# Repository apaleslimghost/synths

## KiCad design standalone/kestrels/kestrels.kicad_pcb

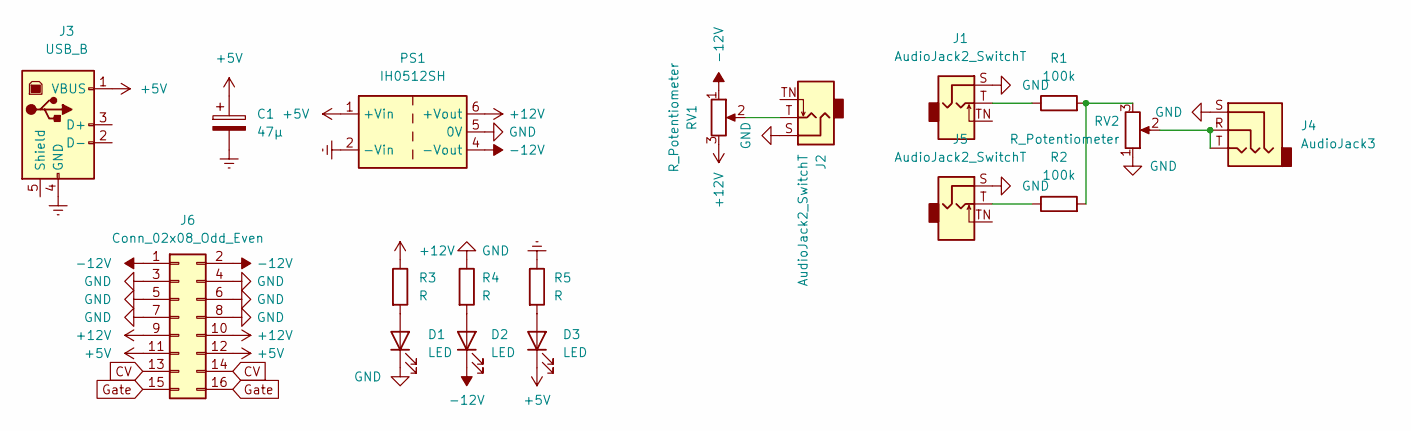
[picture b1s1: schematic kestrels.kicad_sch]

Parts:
C1: 47μ; CP_Radial_D5.0mm_P2.50mm
D1, D2, D3: LED; LED_D3.0mm
J1, J2, J5: AudioJack2_SwitchT; Jack_3.5mm_QingPu_WQP-PJ398SM_Vertical
J3: USB_B; USB_B_Lumberg_2411_02_Horizontal
J4: AudioJack3; Jack_3.5mm_QingPu_WQP-PJ366ST_Vertical
J6: Conn_02x08_Odd_Even; PinHeader_2x08_P2.54mm_Vertical
PS1: IH0512SH; Converter_DCDC_XP_POWER-IHxxxxSH_THT
R1, R2: 100k; R_Axial_DIN0207_L6.3mm_D2.5mm_P7.62mm_Horizontal
R3, R4, R5: R; R_Axial_DIN0207_L6.3mm_D2.5mm_P7.62mm_Horizontal
RV1, RV2: R_Potentiometer; Potentiometer_Alpha_RD901F-40-00D_Single_Vertical

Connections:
+5V: C1.1, D3.1 (K), J3.1 (VBUS), J6.11, J6.12, PS1.1 (+Vin)
+12V: J6.9, J6.10, PS1.6 (+Vout), R3.1, RV1.3
-12V: D2.1 (K), J6.1, J6.2, PS1.4 (-Vout), RV1.1
CV: J6.13, J6.14
Earth: C1.2, J3.4 (GND), PS1.2 (-Vin), R5.1
GND: D1.1 (K), J1.S, J2.S, J4.S, J5.S, J6.3, J6.4, J6.5, J6.6, J6.7, J6.8, PS1.5 (0V), R4.1, RV2.1
Gate: J6.15, J6.16
unnamed: D1.2 (A), R3.2
unnamed: D2.2 (A), R4.2
unnamed: D3.2 (A), R5.2
unnamed: J1.T, R1.1
unnamed: J2.T, RV1.2
unnamed: J4.R, J4.T, RV2.2
unnamed: J5.T, R2.1
unnamed: R1.2, R2.2, RV2.3

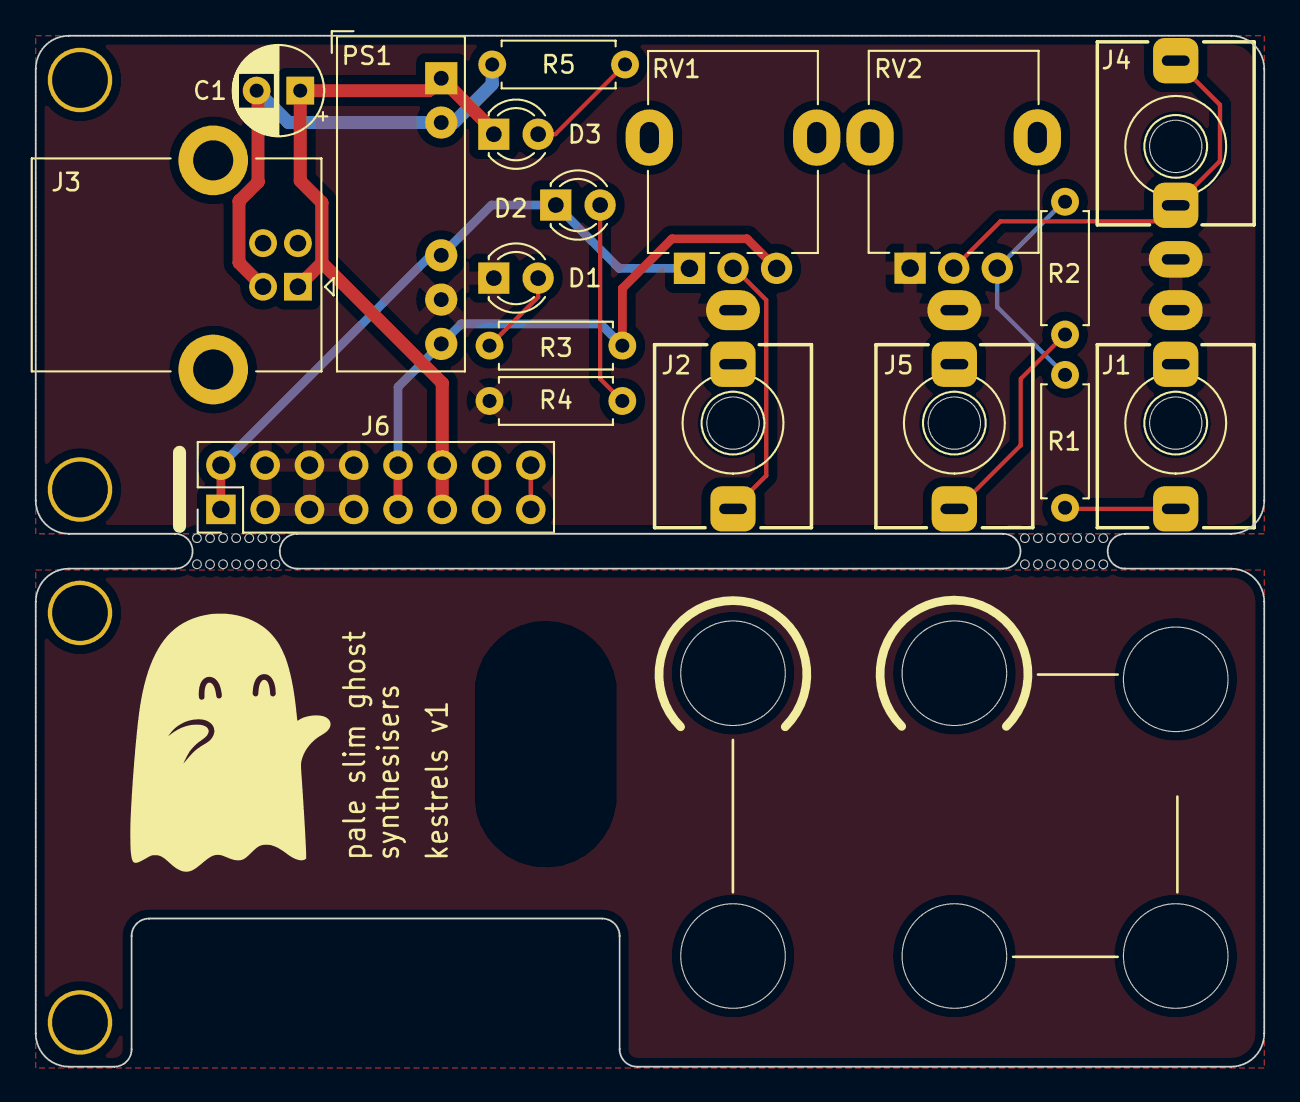
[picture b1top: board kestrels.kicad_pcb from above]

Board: 2 copper layers, 70.5 x 59.2 mm, 20 parts (0 on the bottom side), 15 nets.

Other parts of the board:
mouse-bite-2mm-slot, mouse-bite-2mm-slot#2: VAL**; mousebite-2x5mm

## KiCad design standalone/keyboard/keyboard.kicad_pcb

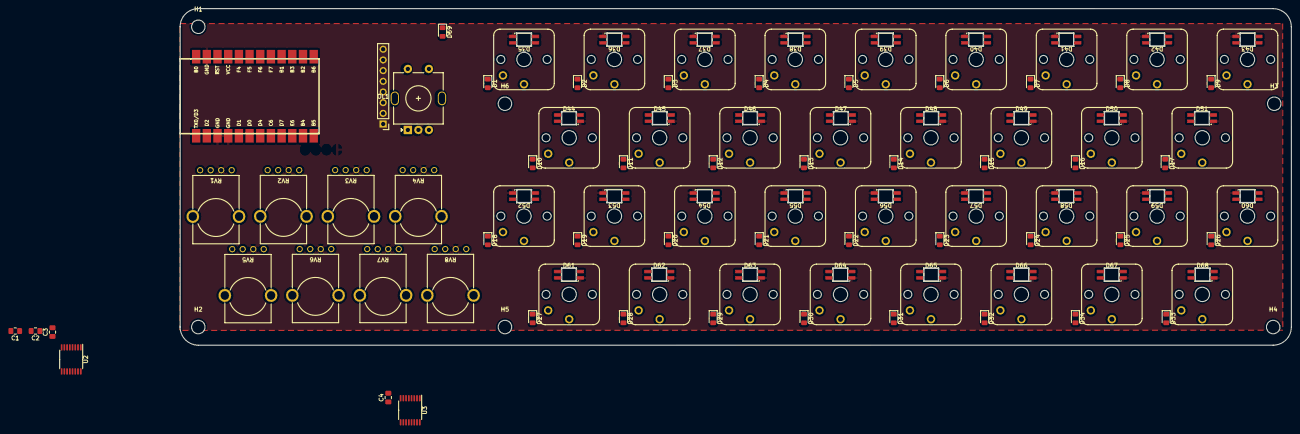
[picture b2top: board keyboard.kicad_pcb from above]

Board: 2 copper layers, 264.2 x 80.0 mm, 126 parts (0 on the bottom side), 104 nets, no tracks yet.

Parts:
C1, C2, C3, C4: C; C_0805_2012Metric_Pad1.18x1.45mm_HandSolder
D1, D2, D3, D4, D5, D6, D7, D8, D9, D10, D11, D12, D13, D14, D15, D16, D17, D18, D19, D20, D21, D22, D23, D24, D25, D26, D27, D28, D29, D30, D31, D32, D33, D34, D69: D; D_0805_2012Metric_Pad1.15x1.40mm_HandSolder
D35, D36, D37, D38, D39, D40, D41, D42, D43, D44, D45, D46, D47, D48, D49, D50, D51, D52, D53, D54, D55, D56, D57, D58, D59, D60, D61, D62, D63, D64, D65, D66, D67, D68: SK6812MINI; SK6812MINI-E
H1, H2, H3, H4, H5, H6: MountingHole; MountingHole_3.2mm_M3
OL1: WaveShare_OLED; WaveShare OLED 1.5 inch
RV1, RV2, RV3, RV4, RV5, RV6, RV7, RV8: R_Potentiometer_Endless; Alpha RV112FF
SW1, SW2, SW3, SW4, SW5, SW6, SW7, SW8, SW9, SW10, SW11, SW12, SW13, SW14, SW15, SW16, SW17, SW18, SW19, SW20, SW21, SW22, SW23, SW24, SW25, SW26, SW27, SW28, SW29, SW30, SW31, SW32, SW33, SW34: SW_Push; Kailh Choc V1
SW35: RotaryEncoder_Switch; RotaryEncoder_EC11
U1: ProMicro; Elite-C-castellated-24pin
U2, U3: ADS7828; TSSOP-16_4.4x5mm_P0.65mm

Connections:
+5V: C3.1, C4.1, D35.1 (VDD), D36.1 (VDD), D37.1 (VDD), D38.1 (VDD), D39.1 (VDD), D40.1 (VDD), D41.1 (VDD), D42.1 (VDD), D43.1 (VDD), D44.1 (VDD), D45.1 (VDD), D46.1 (VDD), D47.1 (VDD), D48.1 (VDD), D49.1 (VDD), D50.1 (VDD), D51.1 (VDD), D52.1 (VDD), D53.1 (VDD), D54.1 (VDD), D55.1 (VDD), D56.1 (VDD), D57.1 (VDD), D58.1 (VDD), D59.1 (VDD), D60.1 (VDD), D61.1 (VDD), D62.1 (VDD), D63.1 (VDD), D64.1 (VDD), D65.1 (VDD), D66.1 (VDD), D67.1 (VDD), D68.1 (VDD), RV1.3, RV2.3, RV3.3, RV4.3, RV5.3, RV6.3, RV7.3, RV8.3, U1.21 (VCC), U2.10 (REF), U2.16 (VDD), U3.10 (REF), U3.16 (VDD)
Col 1: SW1.1, SW10.1, SW18.1, SW27.1, U1.20 (F4)
Col 2: SW2.1, SW11.1, SW19.1, SW28.1, U1.19 (F5)
Col 3: SW3.1, SW12.1, SW20.1, SW29.1, U1.18 (F6)
Col 4: SW4.1, SW13.1, SW21.1, SW30.1, U1.17 (F7)
Col 5: SW5.1, SW14.1, SW22.1, SW31.1, U1.16 (B1)
Col 6: SW6.1, SW15.1, SW23.1, SW32.1, U1.15 (B3)
Col 7: SW7.1, SW16.1, SW24.1, SW33.1, U1.14 (B2)
Col 8: SW8.1, SW17.1, SW25.1, SW34.1, U1.13 (B6)
Col 9: SW9.1, SW26.1, SW35.S2, U1.12 (B5)
Enc A: C1.2, SW35.A, U1.1 (TX)
Enc B: C2.1, SW35.B, U1.2 (RX)
GND: C1.1, C2.2, C3.2, C4.2, D35.3 (VSS), D36.3 (VSS), D37.3 (VSS), D38.3 (VSS), D39.3 (VSS), D40.3 (VSS), D41.3 (VSS), D42.3 (VSS), D43.3 (VSS), D44.3 (VSS), D45.3 (VSS), D46.3 (VSS), D47.3 (VSS), D48.3 (VSS), D49.3 (VSS), D50.3 (VSS), D51.3 (VSS), D52.3 (VSS), D53.3 (VSS), D54.3 (VSS), D55.3 (VSS), D56.3 (VSS), D57.3 (VSS), D58.3 (VSS), D59.3 (VSS), D60.3 (VSS), D61.3 (VSS), D62.3 (VSS), D63.3 (VSS), D64.3 (VSS), D65.3 (VSS), D66.3 (VSS), D67.3 (VSS), D68.3 (VSS), RV1.1, RV2.1, RV3.1, RV4.1, RV5.1, RV6.1, RV7.1, RV8.1, SW35.C, U1.3 (GND), U1.4 (GND), U1.23 (GND), U2.9 (GND), U2.11 (COM), U2.12 (A0), U2.13 (A1), U3.9 (GND), U3.11 (COM), U3.12 (A0), U3.13 (A1)
LED: D35.4 (DIN), U1.11 (B4)
unnamed: D1.1 (K), SW1.2
unnamed: D2.1 (K), SW2.2
unnamed: D3.1 (K), SW3.2
unnamed: D4.1 (K), SW4.2
unnamed: D5.1 (K), SW5.2
unnamed: D6.1 (K), SW6.2
unnamed: D7.1 (K), SW7.2
unnamed: D8.1 (K), SW8.2
unnamed: D9.1 (K), SW9.2
unnamed: D10.1 (K), SW10.2
unnamed: D11.1 (K), SW11.2
unnamed: D12.1 (K), SW12.2
unnamed: D13.1 (K), SW13.2
unnamed: D14.1 (K), SW14.2
unnamed: D15.1 (K), SW15.2
unnamed: D16.1 (K), SW16.2
unnamed: D17.1 (K), SW17.2
unnamed: D18.1 (K), SW18.2
unnamed: D19.1 (K), SW19.2
unnamed: D20.1 (K), SW20.2
unnamed: D21.1 (K), SW21.2
unnamed: D22.1 (K), SW22.2
unnamed: D23.1 (K), SW23.2
unnamed: D24.1 (K), SW24.2
unnamed: D25.1 (K), SW25.2
unnamed: D26.1 (K), SW26.2
unnamed: D27.1 (K), SW27.2
unnamed: D28.1 (K), SW28.2
unnamed: D29.1 (K), SW29.2
unnamed: D30.1 (K), SW30.2
unnamed: D31.1 (K), SW31.2
unnamed: D32.1 (K), SW32.2
unnamed: D33.1 (K), SW33.2
unnamed: D34.1 (K), SW34.2
unnamed: D35.2 (DOUT), D36.4 (DIN)
unnamed: D36.2 (DOUT), D37.4 (DIN)
unnamed: D37.2 (DOUT), D38.4 (DIN)
unnamed: D38.2 (DOUT), D39.4 (DIN)
unnamed: D39.2 (DOUT), D40.4 (DIN)
unnamed: D40.2 (DOUT), D41.4 (DIN)
unnamed: D41.2 (DOUT), D42.4 (DIN)
unnamed: D42.2 (DOUT), D43.4 (DIN)
unnamed: D43.2 (DOUT), D51.4 (DIN)
unnamed: D44.2 (DOUT), D52.4 (DIN)
unnamed: D44.4 (DIN), D45.2 (DOUT)
unnamed: D45.4 (DIN), D46.2 (DOUT)
unnamed: D46.4 (DIN), D47.2 (DOUT)
unnamed: D47.4 (DIN), D48.2 (DOUT)
unnamed: D48.4 (DIN), D49.2 (DOUT)
unnamed: D49.4 (DIN), D50.2 (DOUT)
unnamed: D50.4 (DIN), D51.2 (DOUT)
unnamed: D52.2 (DOUT), D53.4 (DIN)
unnamed: D53.2 (DOUT), D54.4 (DIN)
unnamed: D54.2 (DOUT), D55.4 (DIN)
unnamed: D55.2 (DOUT), D56.4 (DIN)
unnamed: D56.2 (DOUT), D57.4 (DIN)
unnamed: D57.2 (DOUT), D58.4 (DIN)
unnamed: D58.2 (DOUT), D59.4 (DIN)
unnamed: D59.2 (DOUT), D60.4 (DIN)
unnamed: D60.2 (DOUT), D68.4 (DIN)
unnamed: D61.4 (DIN), D62.2 (DOUT)
unnamed: D62.4 (DIN), D63.2 (DOUT)
unnamed: D63.4 (DIN), D64.2 (DOUT)
unnamed: D64.4 (DIN), D65.2 (DOUT)
unnamed: D65.4 (DIN), D66.2 (DOUT)
unnamed: D66.4 (DIN), D67.2 (DOUT)
unnamed: D67.4 (DIN), D68.2 (DOUT)
unnamed: D69.1 (K), SW35.S1
Pot 1A: RV1.2×, U2.8 (CH7)
Pot 1B: RV1.×2, U2.7 (CH6)
Pot 2A: RV2.2×, U2.6 (CH5)
Pot 2B: RV2.×2, U2.5 (CH4)
Pot 3A: RV3.2×, U2.4 (CH3)
Pot 3B: RV3.×2, U2.3 (CH2)
Pot 4A: RV4.2×, U2.2 (CH1)
Pot 4B: RV4.×2, U2.1 (CH0)
Pot 5A: RV5.2×, U3.8 (CH7)
Pot 5B: RV5.×2, U3.7 (CH6)
Pot 6A: RV6.2×, U3.6 (CH5)
Pot 6B: RV6.×2, U3.5 (CH4)
Pot 7A: RV7.2×, U3.4 (CH3)
Pot 7B: RV7.×2, U3.3 (CH2)
Pot 8A: RV8.2×, U3.2 (CH1)
Pot 8B: RV8.×2, U3.1 (CH0)
Row 1: D1.2 (A), D2.2 (A), D3.2 (A), D4.2 (A), D5.2 (A), D6.2 (A), D7.2 (A), D8.2 (A), D9.2 (A), U1.7 (D4)
Row 2: D10.2 (A), D11.2 (A), D12.2 (A), D13.2 (A), D14.2 (A), D15.2 (A), D16.2 (A), D17.2 (A), D69.2 (A), U1.8 (C6)
Row 3: D18.2 (A), D19.2 (A), D20.2 (A), D21.2 (A), D22.2 (A), D23.2 (A), D24.2 (A), D25.2 (A), D26.2 (A), U1.9 (D7)
Row 4: D27.2 (A), D28.2 (A), D29.2 (A), D30.2 (A), D31.2 (A), D32.2 (A), D33.2 (A), D34.2 (A), U1.10 (E6)
SCL: U1.6 (SCL), U2.14 (SCL), U3.14 (SCL)
SDA: U1.5 (SDA), U2.15 (SDA), U3.15 (SDA)

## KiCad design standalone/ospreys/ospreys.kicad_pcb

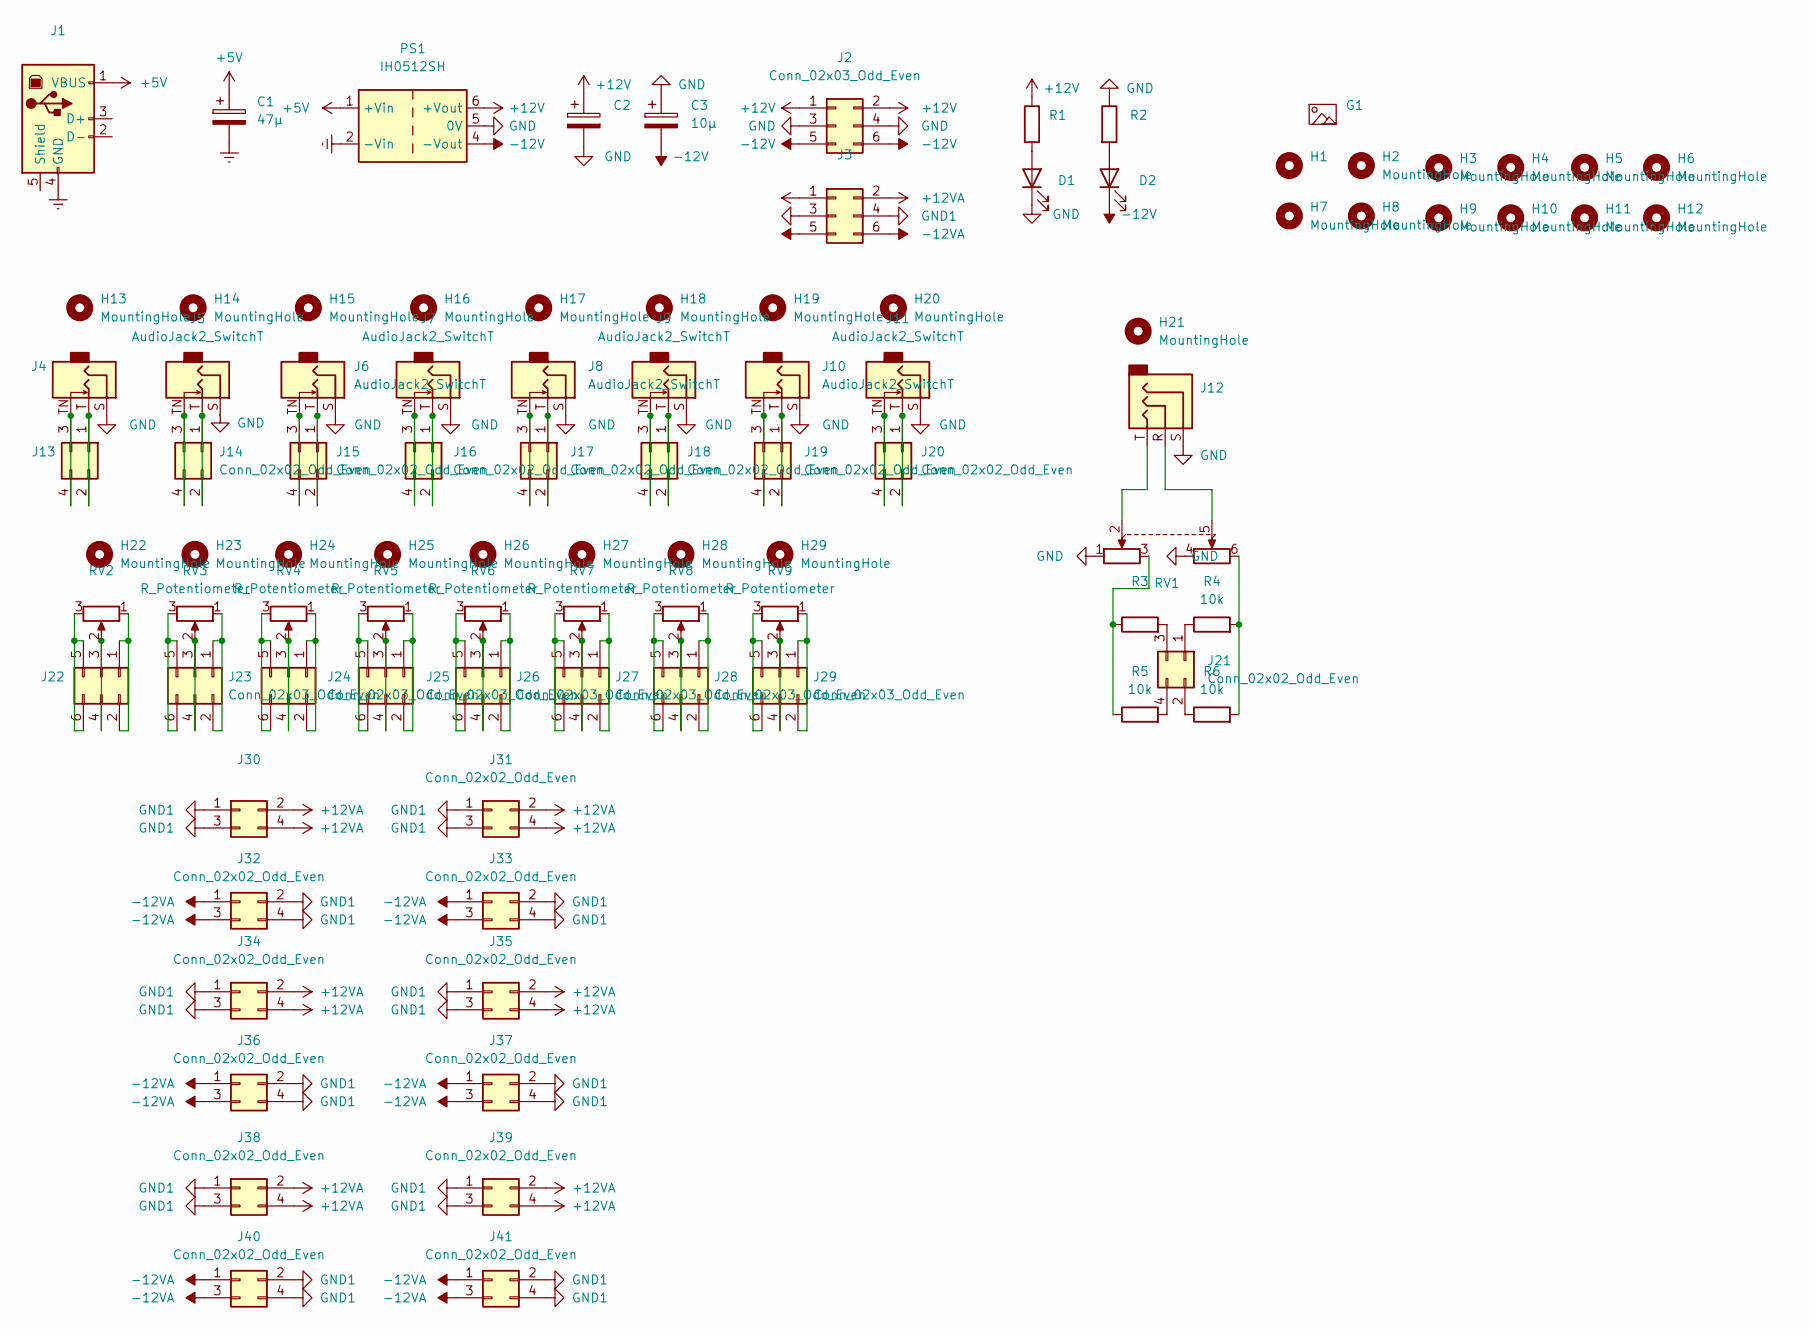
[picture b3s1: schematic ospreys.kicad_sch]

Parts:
C1: 47μ
C2: (no value)
C3: 10μ
D1, D2: (no value)
G1: (no value)
H1: (no value)
H2, H3, H4, H5, H6, H13, H14, H15, H16, H17, H18, H19, H20, H21, H22, H23, H24, H25, H26, H27, H28, H29: MountingHole
H7, H8, H9, H10, H11, H12: MountingHole; MountingHole_3.2mm_M3
J1, J3, J4, J12, J13, J22, J30: (no value)
J2: Conn_02x03_Odd_Even; PinSocket_2x03_P2.54mm_Vertical_SMD
J5, J6, J7, J8, J9, J10, J11: AudioJack2_SwitchT
J14, J15, J16, J17, J18, J19, J20, J21, J32: Conn_02x02_Odd_Even
J23, J24, J25, J26, J27, J28, J29: Conn_02x03_Odd_Even
J31, J33, J34, J35, J36, J37, J38, J39, J40, J41: Conn_02x02_Odd_Even; PinHeader_2x02_P2.54mm_Vertical_SMD
PS1: IH0512SH; Converter_DCDC_XP_POWER-IHxxxxSH_THT
R1, R2: (no value)
R3: R_0805_2012Metric_Pad1.20x1.40mm_HandSolder
R4, R5, R6: 10k; R_0805_2012Metric_Pad1.20x1.40mm_HandSolder
RV1, RV2: (no value)
RV3, RV4, RV5, RV6, RV7, RV8, RV9: R_Potentiometer

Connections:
+5V: C1.1, J1.1 (VBUS), PS1.1 (+Vin)
+12V: C2.1, J2.1, J2.2, PS1.6 (+Vout), R1.1
-12V: C3.2, D2.1 (K), J2.5, J2.6, PS1.4 (-Vout)
Earth: C1.2, J1.4 (GND), PS1.2 (-Vin)
GND: C2.2, C3.1, D1.1 (K), J2.3, J2.4, J4.S, J5.S, J6.S, J7.S, J8.S, J9.S, J10.S, J11.S, J12.S, PS1.5 (0V), R2.1, RV1.1, RV1.4
unnamed: D1.2 (A), R1.2
unnamed: D2.2 (A), R2.2
unnamed: J10.T, J19.1, J19.2
unnamed: J10.TN, J19.3, J19.4
unnamed: J11.T, J20.1, J20.2
unnamed: J11.TN, J20.3, J20.4
unnamed: J12.R, RV1.5
unnamed: J12.T, RV1.2
unnamed: J4.T, J13.1, J13.2
unnamed: J4.TN, J13.3, J13.4
unnamed: J5.T, J14.1
unnamed: J5.TN, J14.3
unnamed: J6.T, J15.1, J15.2
unnamed: J6.TN, J15.3, J15.4
unnamed: J7.T, J16.1, J16.2
unnamed: J7.TN, J16.3, J16.4
unnamed: J8.T, J17.1, J17.2
unnamed: J8.TN, J17.3, J17.4
unnamed: J9.T, J18.1, J18.2
unnamed: J9.TN, J18.3, J18.4
unnamed: J21.1, R4.1
unnamed: J21.2, R6.1
unnamed: J21.3, R3.2
unnamed: J21.4, R5.2
unnamed: J22.1, J22.2, RV2.1
unnamed: J22.3, J22.4, RV2.2
unnamed: J22.5, J22.6, RV2.3
unnamed: J23.1, J23.2, RV3.1
unnamed: J23.3, J23.4, RV3.2
unnamed: J23.5, J23.6, RV3.3
unnamed: J24.1, J24.2, RV4.1
unnamed: J24.3, J24.4, RV4.2
unnamed: J24.5, J24.6, RV4.3
unnamed: J25.1, J25.2, RV5.1
unnamed: J25.3, J25.4, RV5.2
unnamed: J25.5, J25.6, RV5.3
unnamed: J26.1, J26.2, RV6.1
unnamed: J26.3, J26.4, RV6.2
unnamed: J26.5, J26.6, RV6.3
unnamed: J27.1, J27.2, RV7.1
unnamed: J27.3, J27.4, RV7.2
unnamed: J27.5, J27.6, RV7.3
unnamed: J28.1, J28.2, RV8.1
unnamed: J28.3, J28.4, RV8.2
unnamed: J28.5, J28.6, RV8.3
unnamed: J29.1, J29.2, RV9.1
unnamed: J29.3, J29.4, RV9.2
unnamed: J29.5, J29.6, RV9.3
unnamed: R3.1, R5.1, RV1.3
unnamed: R4.2, R6.2, RV1.6

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
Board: 2 copper layers, 92 parts (0 on the bottom side), 58 nets, no tracks yet.
